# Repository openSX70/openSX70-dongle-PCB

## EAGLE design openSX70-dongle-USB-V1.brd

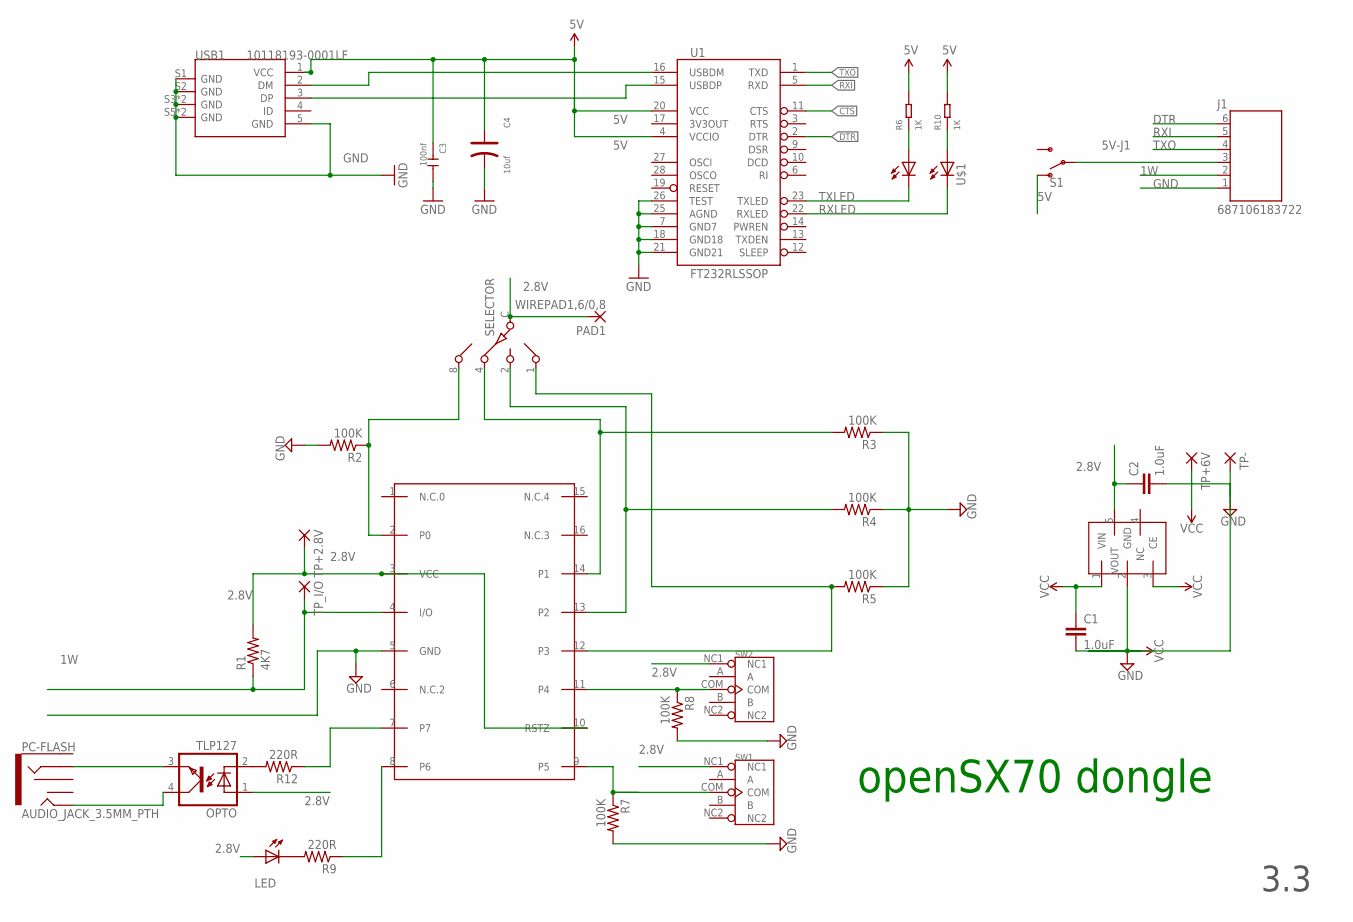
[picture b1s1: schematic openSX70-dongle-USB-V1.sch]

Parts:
C1, C2: 1.0uF; C0603
C3: 100nf; C0603
C4: 10uf; AVX-A
DS2408: DS2408; SO16
J1: 687106183722
LED: LED3MM
OPTO: TLP127; SO-4
PAD1: WIREPAD1,6/0,8; 1,6/0,8
PC-FLASH: AUDIO_JACK_3.5MM_PTH; AUDIO-JACK
R1: 4K7; M0805
R2, R3, R4, R5, R7, R8: 100K; M0805
R6, R10: 1K; R0603
R9, R12: 220R; M0805
REG: NCP4688; SOT-23-5
S1: SWITCH-SPDT-SMD-RIGHT-ANGLE; SWITCH_SPST_SMD_A
SELECTOR: SW-C16
SW1, SW2: DIP-TOGGLE-SWITCH-ON-ON(3+2P-8.8X4.6MM)-90D; SW5-2.0-8.8X4.4X4.7MM-90D
TP+2.8V, TP+6V: SMD2; SMD1,27-2,54
TP-: SMD2; SMD1,27-2,54
TP_I/O: SMD2; SMD1,27-2,54
U1: FT232RLSSOP; SSOP28DB
U$1: DUAL-LED-0603-BIS; LED_APHB1608SYKSURKC
USB1: 10118193-0001LF; MICRO-USB5+6P-SMD-0.65-B

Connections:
1W: DS2408.4 (I/O), J1.2 (5), R1.1, TP_I/O.1
2.8V: C2.1, DS2408.3 (VCC), DS2408.10 (RSTZ), LED.A, OPTO.1 (A), PAD1.1, R1.2, REG.5 (VOUT), SELECTOR.C, SW1.NC1, SW2.NC1, TP+2.8V.1
5V: C3.1, C4.+, R6.2, R10.2, S1.1 (O), U1.4 (VCCIO), U1.20 (VCC), USB1.1 (VCC)
5V-J1: J1.3 (4), S1.2
CTS: U1.11 (CTS)
DTR: J1.6 (1), U1.2 (DTR)
GND: C1.2, C2.2, C3.2, C4.-, DS2408.5 (GND), J1.1 (6), R2.2, R3.1, R4.1, R5.1, R7.2, R8.2, REG.2 (GND), TP-.1, U1.7 (GND7), U1.18 (GND18), U1.21 (GND21), U1.25 (AGND), U1.26 (TEST), USB1.5 (GND), USB1.S1 (GND), USB1.S2 (GND), USB1.S3 (GND), USB1.S4 (GND), USB1.S5 (GND), USB1.S6 (GND)
unnamed: LED.K (C), R9.2
unnamed: DS2408.2 (P0), R2.1, SELECTOR.8
unnamed: DS2408.14 (P1), R3.2, SELECTOR.4
unnamed: DS2408.13 (P2), R4.2, SELECTOR.2
unnamed: DS2408.11 (P4), R8.1, SW2.COM
unnamed: DS2408.9 (P5), R7.1, SW1.COM
unnamed: DS2408.8 (P6), R9.1
unnamed: R6.1, U$1.1 (A)
unnamed: OPTO.2 (C), R12.2
unnamed: DS2408.7, R12.1
unnamed: OPTO.4 (COL), PC-FLASH.TIP
unnamed: DS2408.12 (P3), R5.2, SELECTOR.1
unnamed: R10.1, U$1.3 (A1)
unnamed: OPTO.3 (EMIT), PC-FLASH.RING
unnamed: U1.16 (USBDM), USB1.2 (DM)
RXI: J1.5 (2), U1.5 (RXD)
RXLED: U1.22 (RXLED), U$1.4 (C1)
TXLED: U1.23 (TXLED), U$1.2 (C)
TXO: J1.4 (3), U1.1 (TXD)
USB_D+: U1.15 (USBDP), USB1.3 (DP)
VCC: C1.1, REG.1 (VIN), REG.3 (CE), TP+6V.1

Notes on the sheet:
openSX70 dongle
3.3

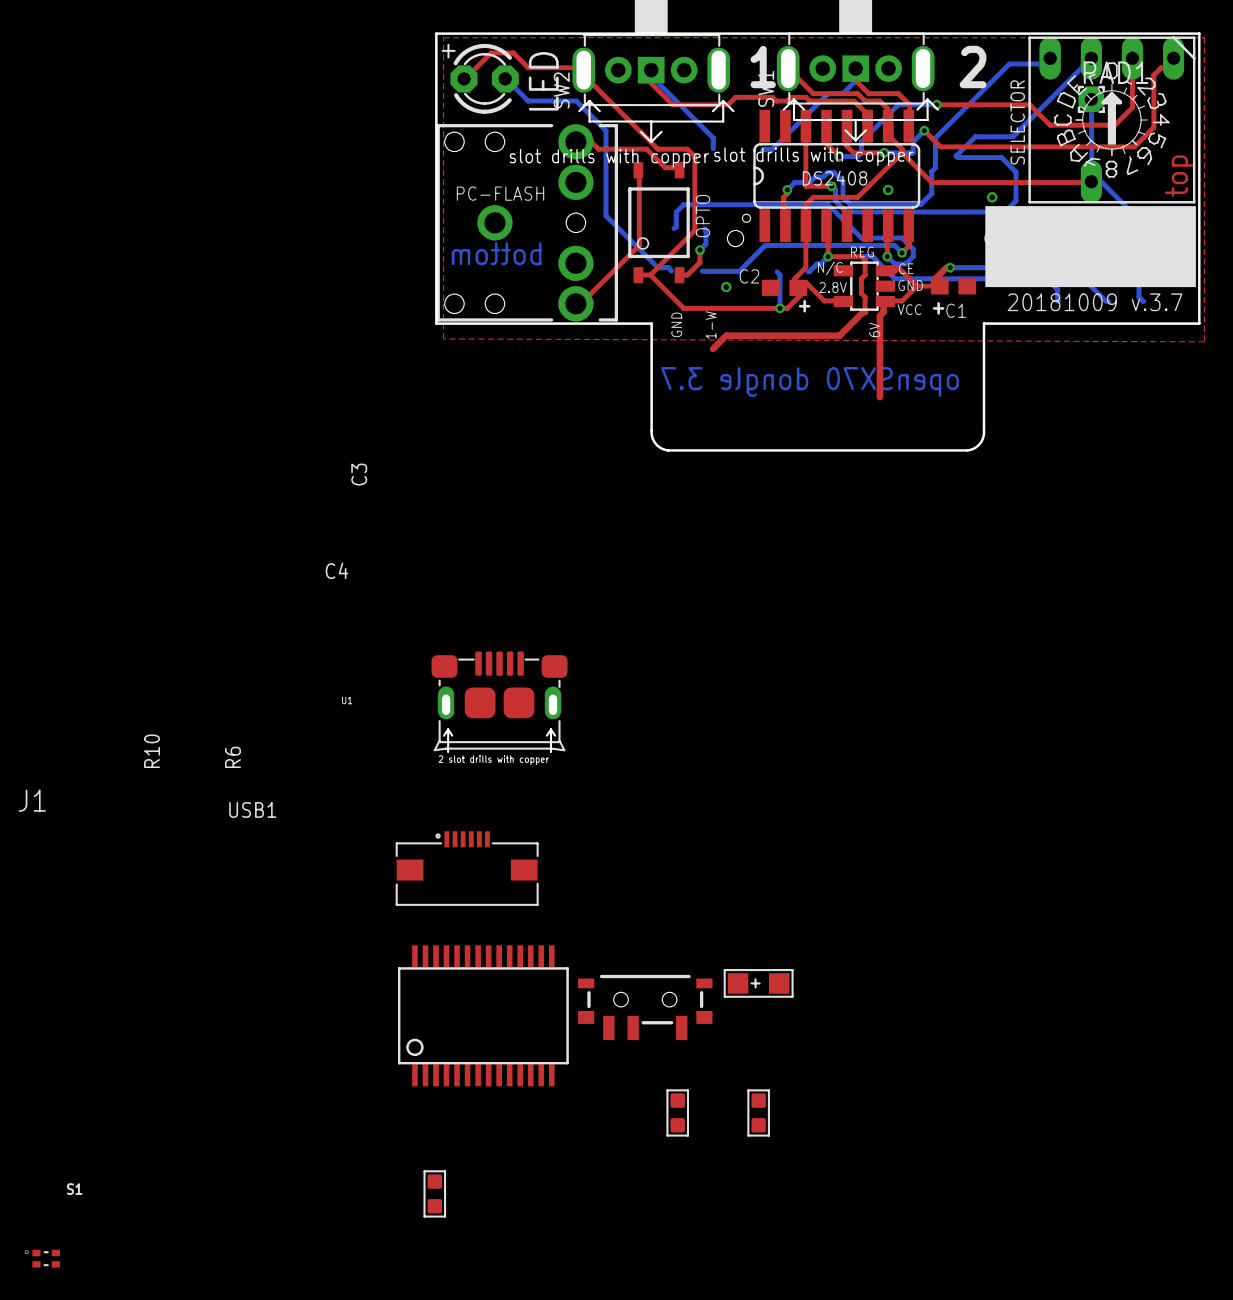
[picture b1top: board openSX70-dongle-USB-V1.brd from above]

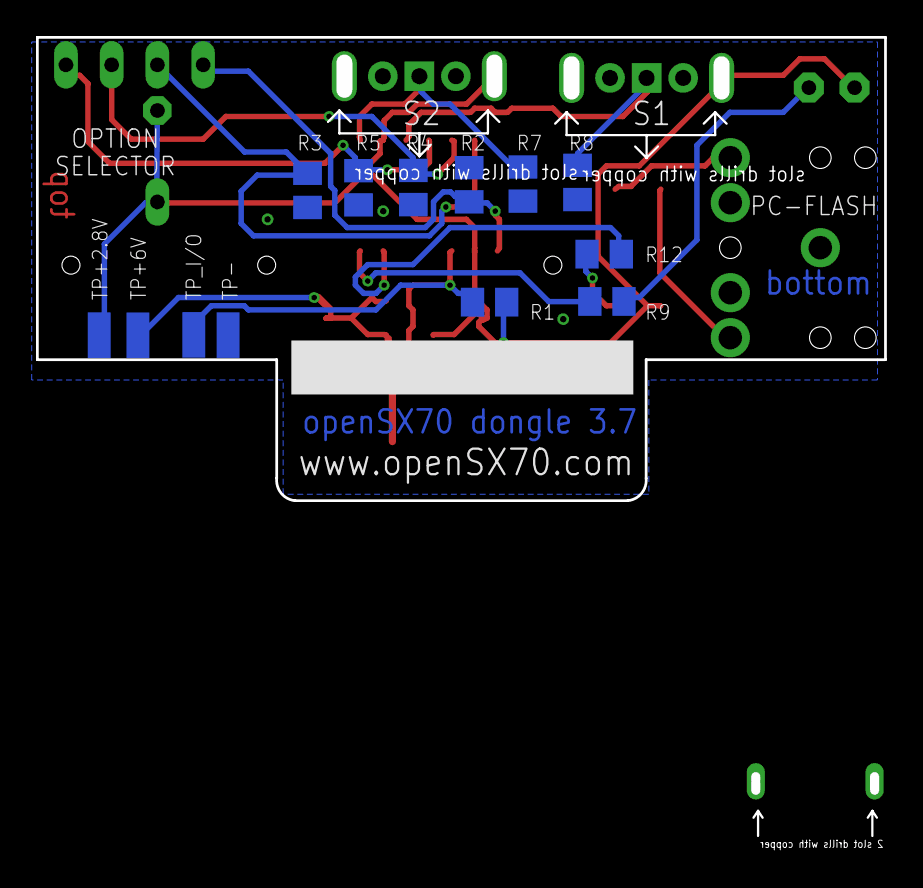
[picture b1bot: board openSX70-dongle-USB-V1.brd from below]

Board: 2 copper layers, 33 parts (13 on the bottom side), 27 nets.

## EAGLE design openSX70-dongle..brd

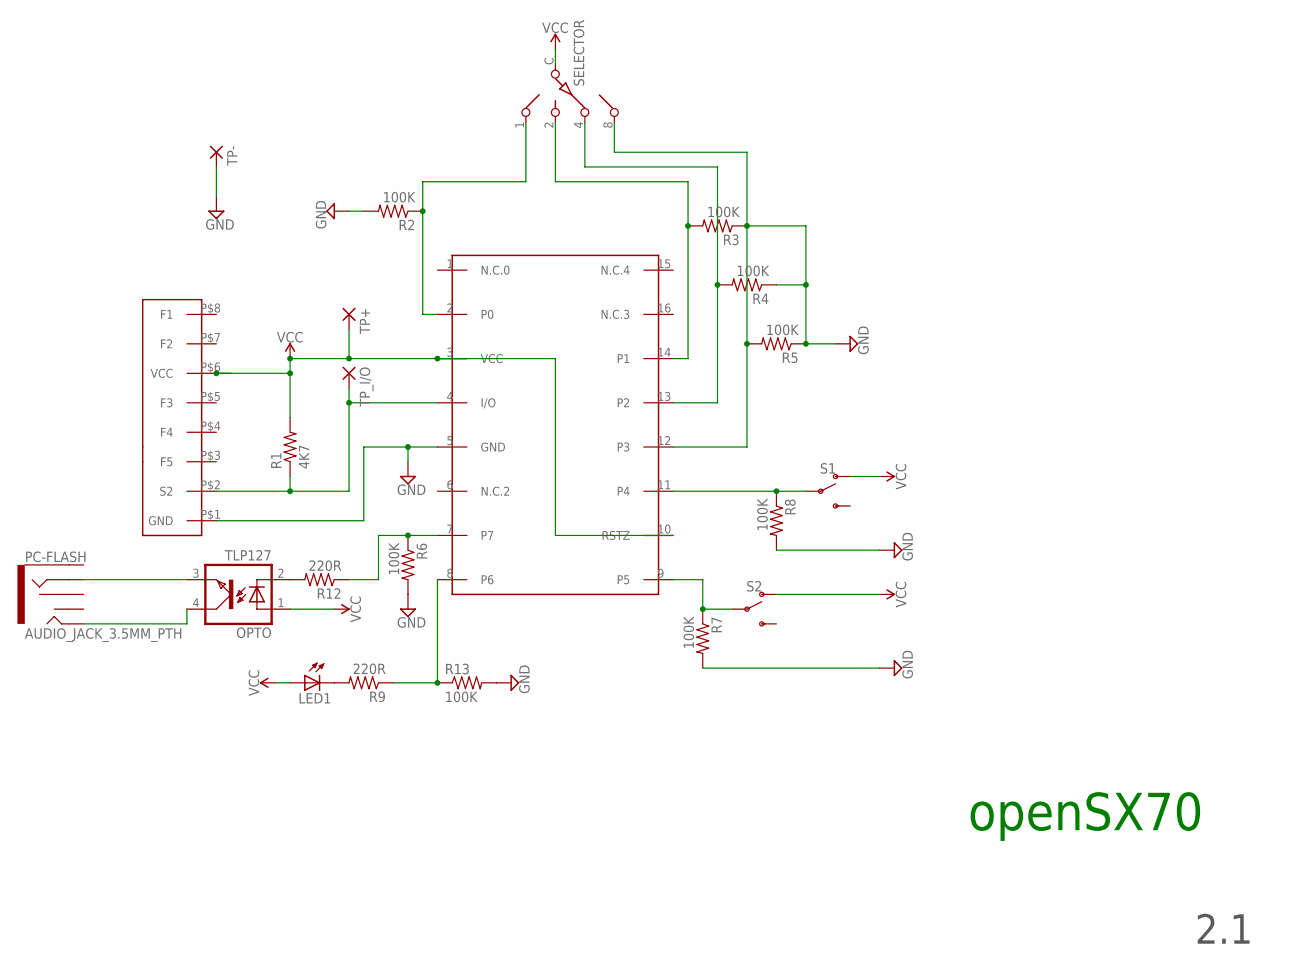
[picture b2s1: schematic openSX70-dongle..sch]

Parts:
DS2408: DS2408; SO16
LED1: LED3MM
OPTO: TLP127; SO-4
PC-FLASH: AUDIO_JACK_3.5MM_PTH; AUDIO-JACK
R1: 4K7; M0805
R2, R3, R4, R5, R6, R7, R8, R13: 100K; M0805
R9, R12: 220R; M0805
S1, S2: SWITCH-SPDT-SMD-RIGHT-ANGLE; SWITCH_SPST_SMD_A
SELECTOR: SW-C16
TP+: SMD2; SMD1,27-2,54
TP-: SMD2; SMD1,27-2,54
TP_I/O: SMD2; SMD1,27-2,54
U$1: FLASH-EDGE-CONNECTOR; FLASH-EDGE-8

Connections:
GND: DS2408.5 (GND), DS2408.12 (P3), R2.2, R3.1, R4.1, R5.1, R5.2, R6.2, R7.2, R8.2, R13.2, SELECTOR.8, TP-.1, U$1.P$1 (GND)
unnamed: DS2408.4 (I/O), R1.1, TP_I/O.1, U$1.P$2 (S2)
unnamed: LED1.K (C), R9.2
unnamed: DS2408.2 (P0), R2.1, SELECTOR.1
unnamed: DS2408.14 (P1), R3.2, SELECTOR.2
unnamed: DS2408.13 (P2), R4.2, SELECTOR.4
unnamed: DS2408.11 (P4), R8.1, S1.2
unnamed: DS2408.9 (P5), R7.1, S2.2
unnamed: DS2408.8 (P6), R9.1, R13.1
unnamed: OPTO.2 (C), R12.2
unnamed: DS2408.7, R6.1, R12.1
unnamed: OPTO.4 (COL), PC-FLASH.TIP
unnamed: OPTO.3 (EMIT), PC-FLASH.RING
VCC: DS2408.3 (VCC), DS2408.10 (RSTZ), LED1.A, OPTO.1 (A), R1.2, S1.1 (O), S2.1 (O), SELECTOR.C, TP+.1, U$1.P$6 (VCC)

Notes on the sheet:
openSX70
2.1

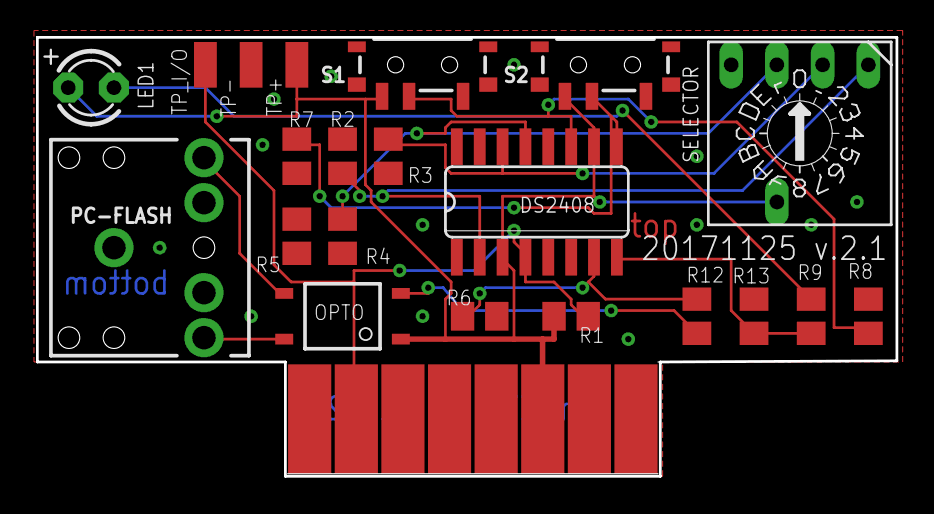
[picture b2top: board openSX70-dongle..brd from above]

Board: 2 copper layers, 47.8 x 24.4 mm, 22 parts (0 on the bottom side), 14 nets.

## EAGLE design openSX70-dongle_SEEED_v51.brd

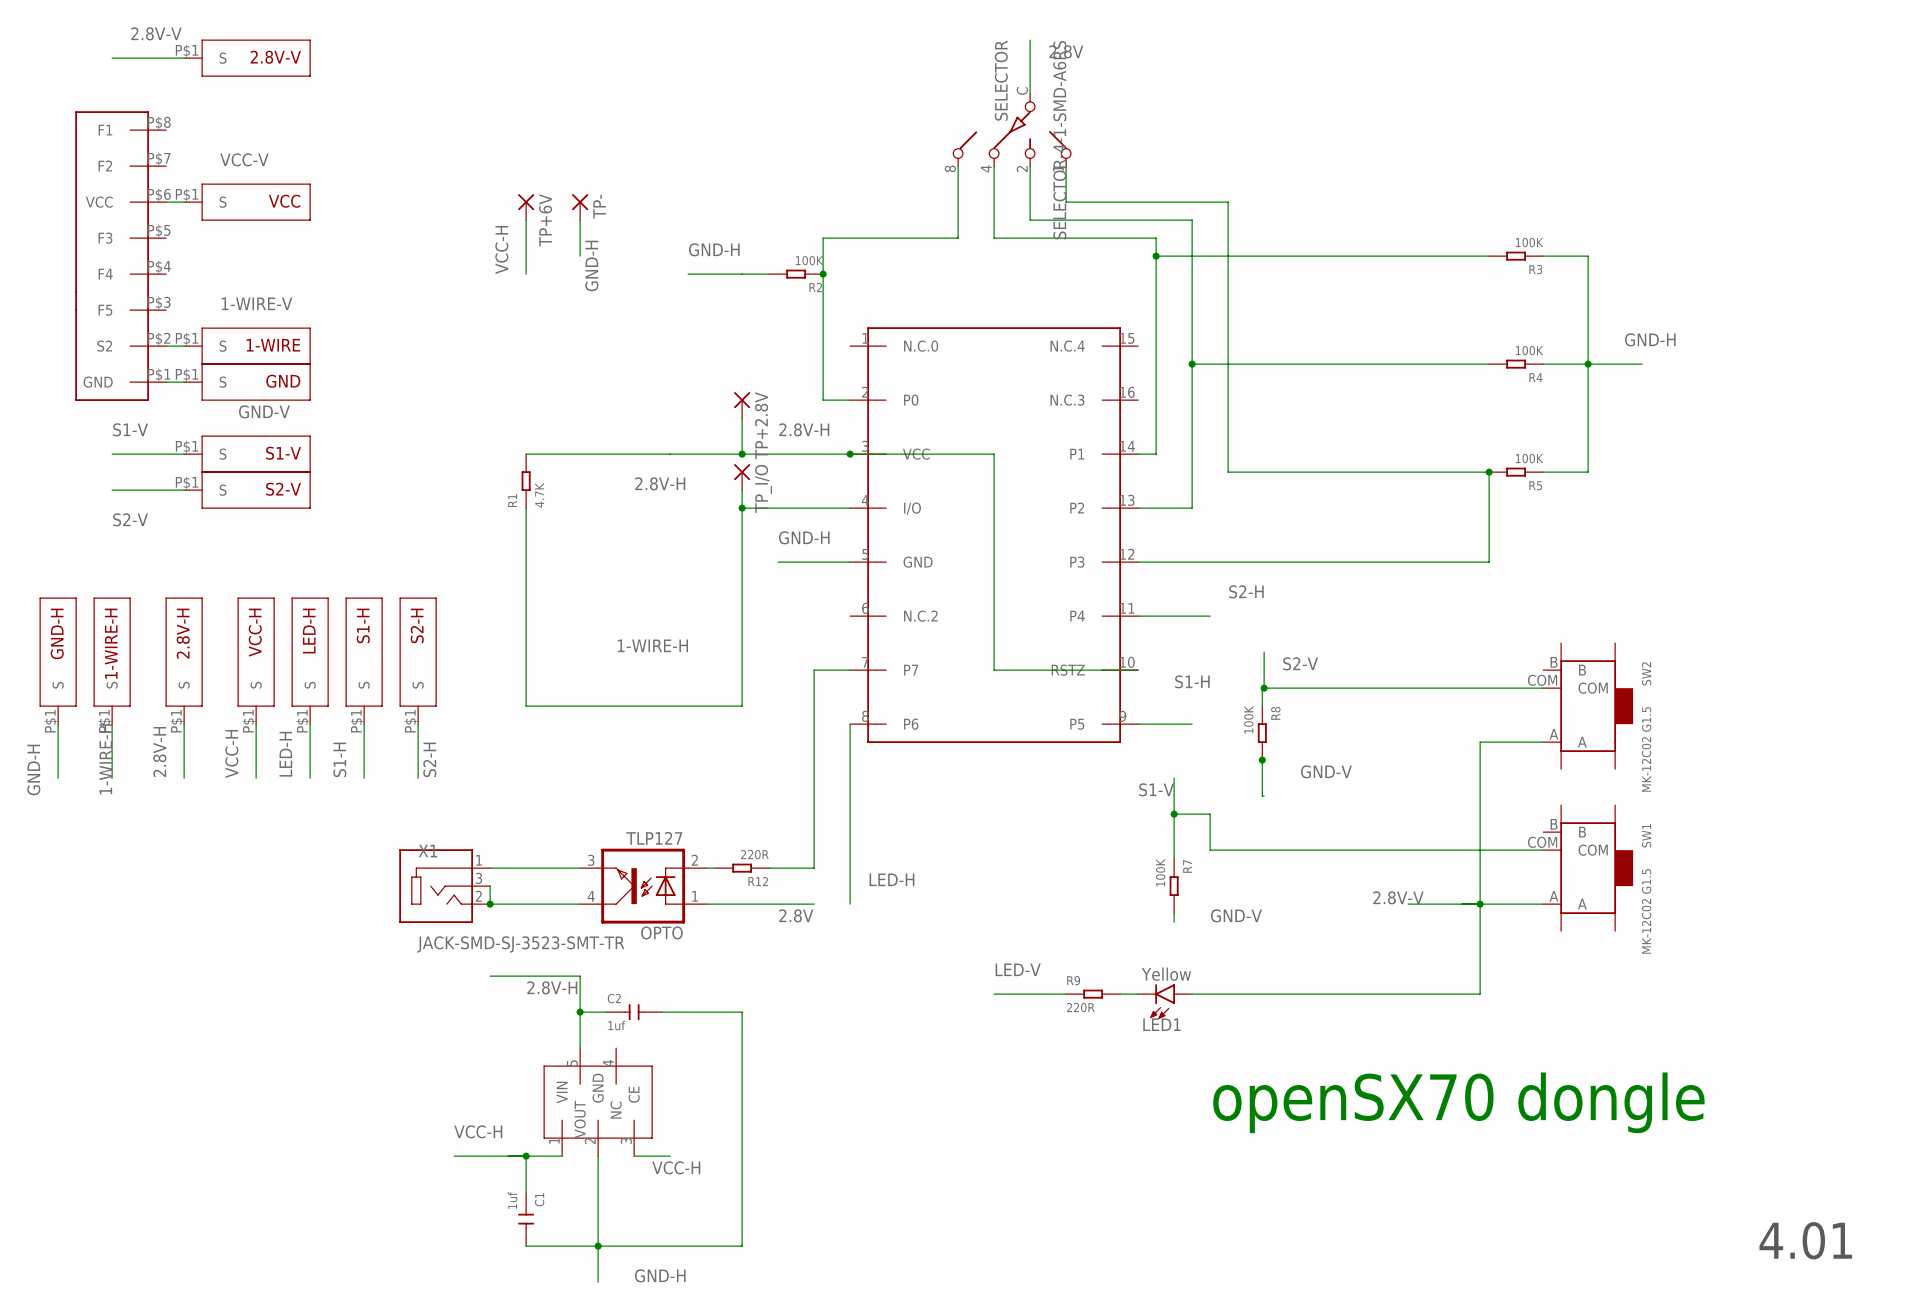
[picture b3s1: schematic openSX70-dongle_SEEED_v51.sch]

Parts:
1-WIRE, 1-WIRE-H, 2.8V-H, 2.8V-V: SX70-S-PAD-NEW; SX70-S-PAD2
C1, C2: 1uf; C0603
DS2408: DS2408; SO16
GND: SX70-S-PAD-NEW; SX70-S-PAD2
GND-H: SX70-S-PAD-NEW; SX70-S-PAD2
LED1: Yellow; LED-1206
LED-H: SX70-S-PAD-NEW; SX70-S-PAD2
OPTO: TLP127; SO-4
R1: 4.7K; R0603
R2, R3, R4, R5, R7, R8: 100K; R0603
R9, R12: 220R; R0603
REG: NCP4688; SOT-23-5
S1-H, S1-V, S2-H, S2-V: SX70-S-PAD-NEW; SX70-S-PAD2
SELECTOR: SELECTOR-4-1-SMD-A6RS; A6RS-161RS
SW1, SW2: MK-12C02 G1.5; SW7-SMD-L6.7X2.7X3.2MM
TP+2.8V, TP+6V: SMD2; SMD1,27-2,54
TP-: SMD2; SMD1,27-2,54
TP_I/O: SMD2; SMD1,27-2,54
U$1: FLASH-EDGE-CONNECTOR; FLASH-EDGE-8
VCC: SX70-S-PAD-NEW; SX70-S-PAD2
VCC-H: SX70-S-PAD-NEW; SX70-S-PAD2
X1: JACK-SMD-SJ-3523-SMT-TR; CUI_SJ-3523-SMT-TR

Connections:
1-WIRE-H: 1-WIRE-H.P$1, DS2408.4 (I/O), R1.1, TP_I/O.1
1-WIRE-V: 1-WIRE.P$1, U$1.P$2 (S2)
2.8V: OPTO.1 (A), SELECTOR.C
2.8V-H: 2.8V-H.P$1, C2.1, DS2408.3 (VCC), DS2408.10 (RSTZ), R1.2, REG.5 (VOUT), TP+2.8V.1
2.8V-V: 2.8V-V.P$1, LED1.A, SW1.A, SW2.A
GND-H: C1.2, C2.2, DS2408.5 (GND), GND-H.P$1, R2.2, R3.1, R4.1, R5.1, REG.2 (GND), TP-.1
GND-V: GND.P$1, R7.2, R8.2, U$1.P$1 (GND)
LED-H: DS2408.8 (P6), LED-H.P$1
LED-V: R9.1
unnamed: OPTO.3 (EMIT), X1.1
unnamed: LED1.C, R9.2
unnamed: DS2408.2 (P0), R2.1, SELECTOR.8
unnamed: DS2408.14 (P1), R3.2, SELECTOR.4
unnamed: DS2408.13 (P2), R4.2, SELECTOR.2
unnamed: OPTO.4 (COL), X1.2, X1.3
unnamed: OPTO.2 (C), R12.2
unnamed: DS2408.7, R12.1
unnamed: DS2408.12 (P3), R5.2, SELECTOR.1
S1-H: DS2408.9 (P5), S1-H.P$1
S1-V: R7.1, S1-V.P$1, SW1.COM
S2-H: DS2408.11 (P4), S2-H.P$1
S2-V: R8.1, S2-V.P$1, SW2.COM
VCC-H: C1.1, REG.1 (VIN), REG.3 (CE), TP+6V.1, VCC-H.P$1
VCC-V: U$1.P$6 (VCC), VCC.P$1

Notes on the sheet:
openSX70 dongle
4.01

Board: 2 copper layers, 37 parts (3 on the bottom side), 23 nets, no tracks yet.

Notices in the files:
parts and their libraries:
SparkFun-Connectors: Licensing: Creative Commons ShareAlike 4.0 International - https://creativecommons.org/licenses/by-sa/4.0
